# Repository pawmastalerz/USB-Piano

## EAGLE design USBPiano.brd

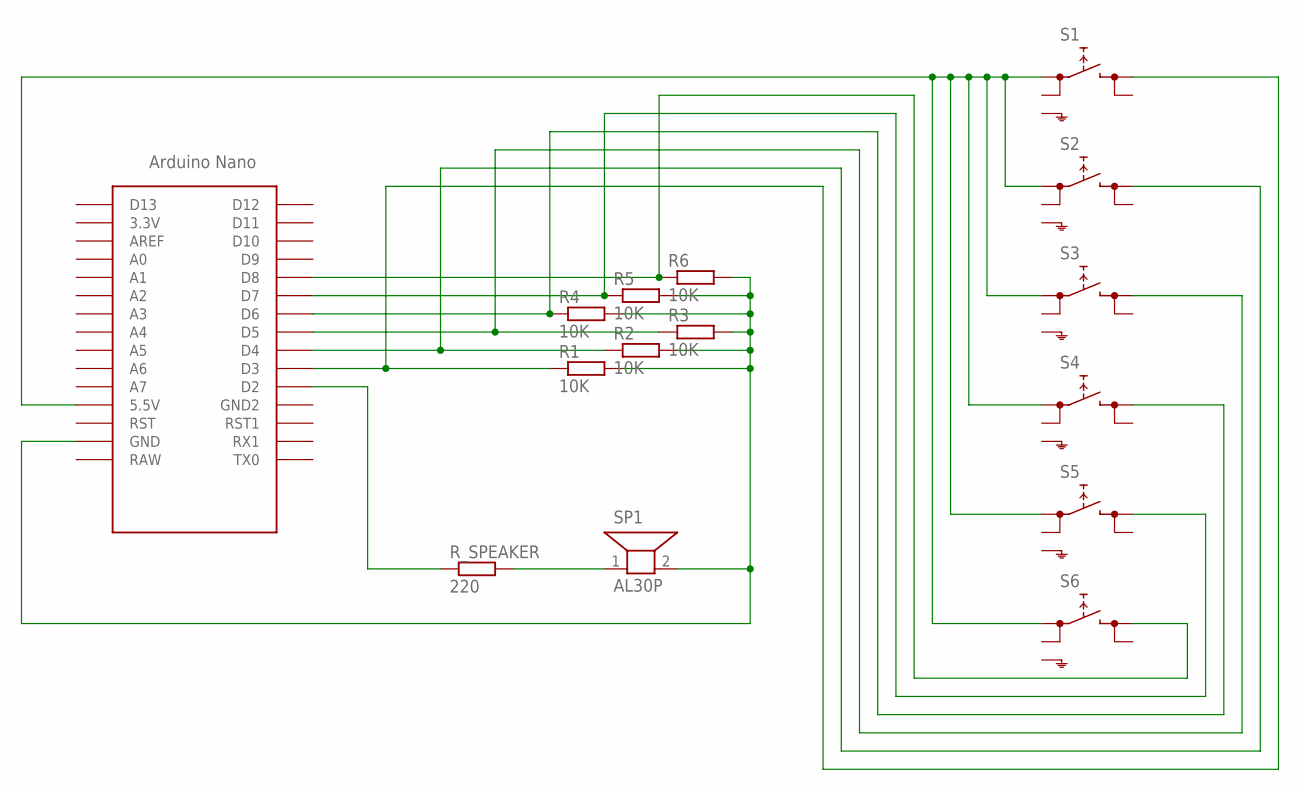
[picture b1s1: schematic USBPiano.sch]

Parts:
R1, R2, R3, R4, R5, R6: 10K; M0805
R_SPEAKER: 220; M0805
S1, S2, S3, S4, S5, S6: SKHMPSE010; SKHMPXE010
SP1: AL30P
U$1: NANO

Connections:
GND: R1.2, R2.2, R3.2, R4.2, R5.2, R6.2, SP1.2, U$1.GND
R_SPEAKER: R_SPEAKER.1, U$1.D2
SPEAKER: R_SPEAKER.2, SP1.1
SWITCH_1: R1.1, S1.3 (2.1), U$1.D3
SWITCH_2: R2.1, S2.3 (2.1), U$1.D4
SWITCH_3: R3.1, S3.3 (2.1), U$1.D5
SWITCH_4: R4.1, S4.3 (2.1), U$1.D6
SWITCH_5: R5.1, S5.3 (2.1), U$1.D7
SWITCH_6: R6.1, S6.3 (2.1), U$1.D8
VCC: S1.1 (1.1), S2.1 (1.1), S3.1 (1.1), S4.1 (1.1), S5.1 (1.1), S6.1 (1.1), U$1.5V (5.5V)

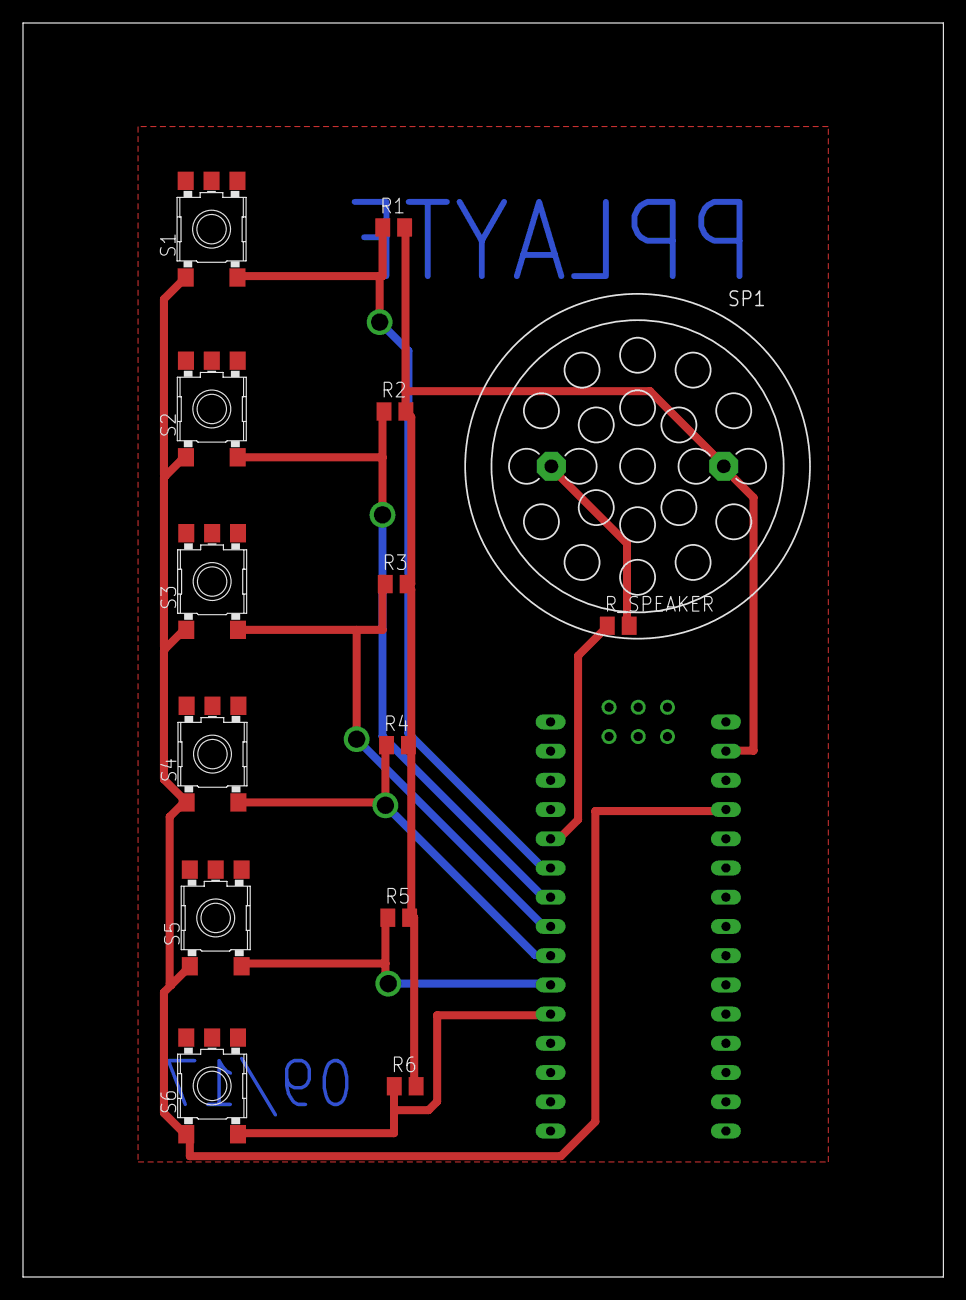
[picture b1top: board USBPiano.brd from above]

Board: 2 copper layers, 80.0 x 109.0 mm, 15 parts (0 on the bottom side), 10 nets.
